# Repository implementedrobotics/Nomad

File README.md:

# NOMAD
NOMAD is a 12-DOF quadruped walking robot using Linear and Nonlinear Optimization Control techniques.

  - Linear and Nonlinear Model Predictive Control
  - Simultaneous Localization and Mapping
  - Remote Control Teleoperation

# Software Installation

First thing to do is setup your software/development environment to build the source code:
[Software Setup](https://github.com/implementedrobotics/Nomad/tree/master/Software).

# Hardware Installation

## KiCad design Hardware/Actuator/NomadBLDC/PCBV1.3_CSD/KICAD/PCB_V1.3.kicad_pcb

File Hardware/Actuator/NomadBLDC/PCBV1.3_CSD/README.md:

# File structure
* Directory - KICAD
** Contains all files for the kicad project
* Directory - KICAD_READERS
** python macros that generated BOM lists for PCBA
* Directory - GERBERS
** plots for PCBA

# Updates from original BK board
* converted from eagle to kicad
* re-routed nearly all traces
* added [CSD88599Q5DC](http://www.ti.com/lit/ds/symlink/csd88599q5dc.pdf?HQS=TI-null-null-mousermode-df-pf-null-wwe&DCM=yes&ref_url=https%3A%2F%2Fwww.mouser.com%2F&distId=26) half-bridge FET
* added more caps
* added power terminal tabs for easier soldering
* added jumper to enable/disable 120 ohm CAN terminating resistor
* added USB connector
* added I/O pin to programming connector
* simplified mask to read all components

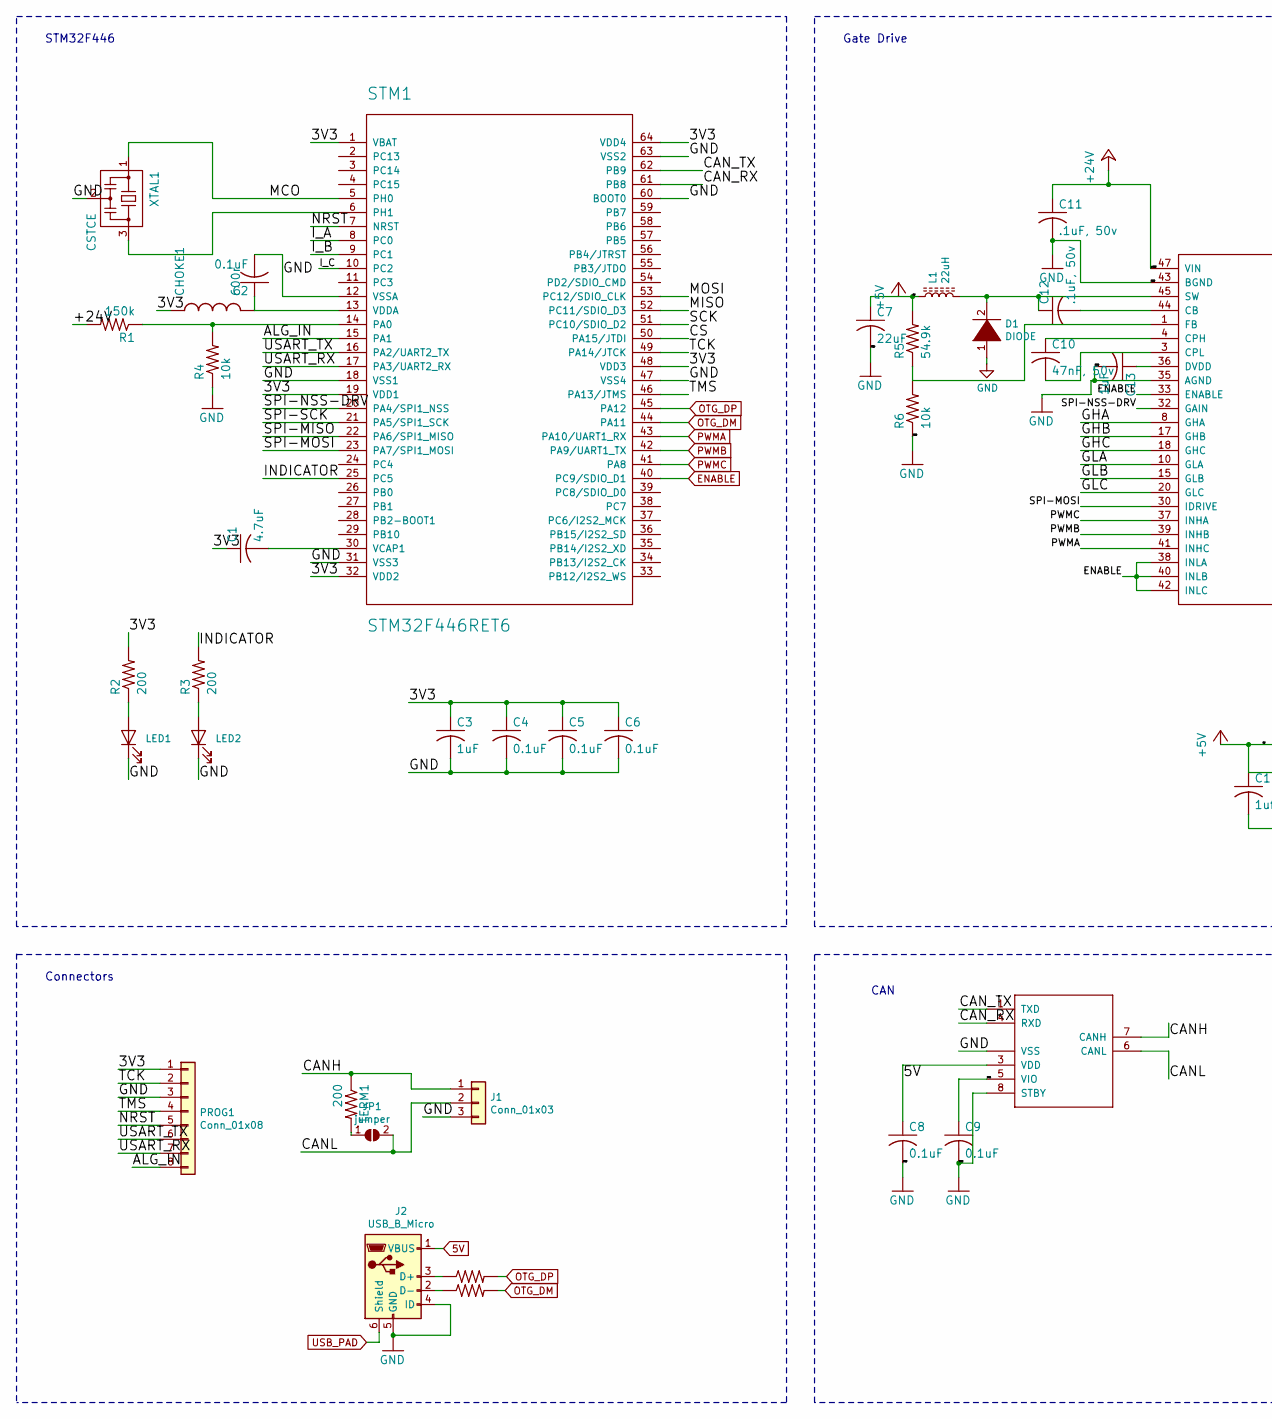
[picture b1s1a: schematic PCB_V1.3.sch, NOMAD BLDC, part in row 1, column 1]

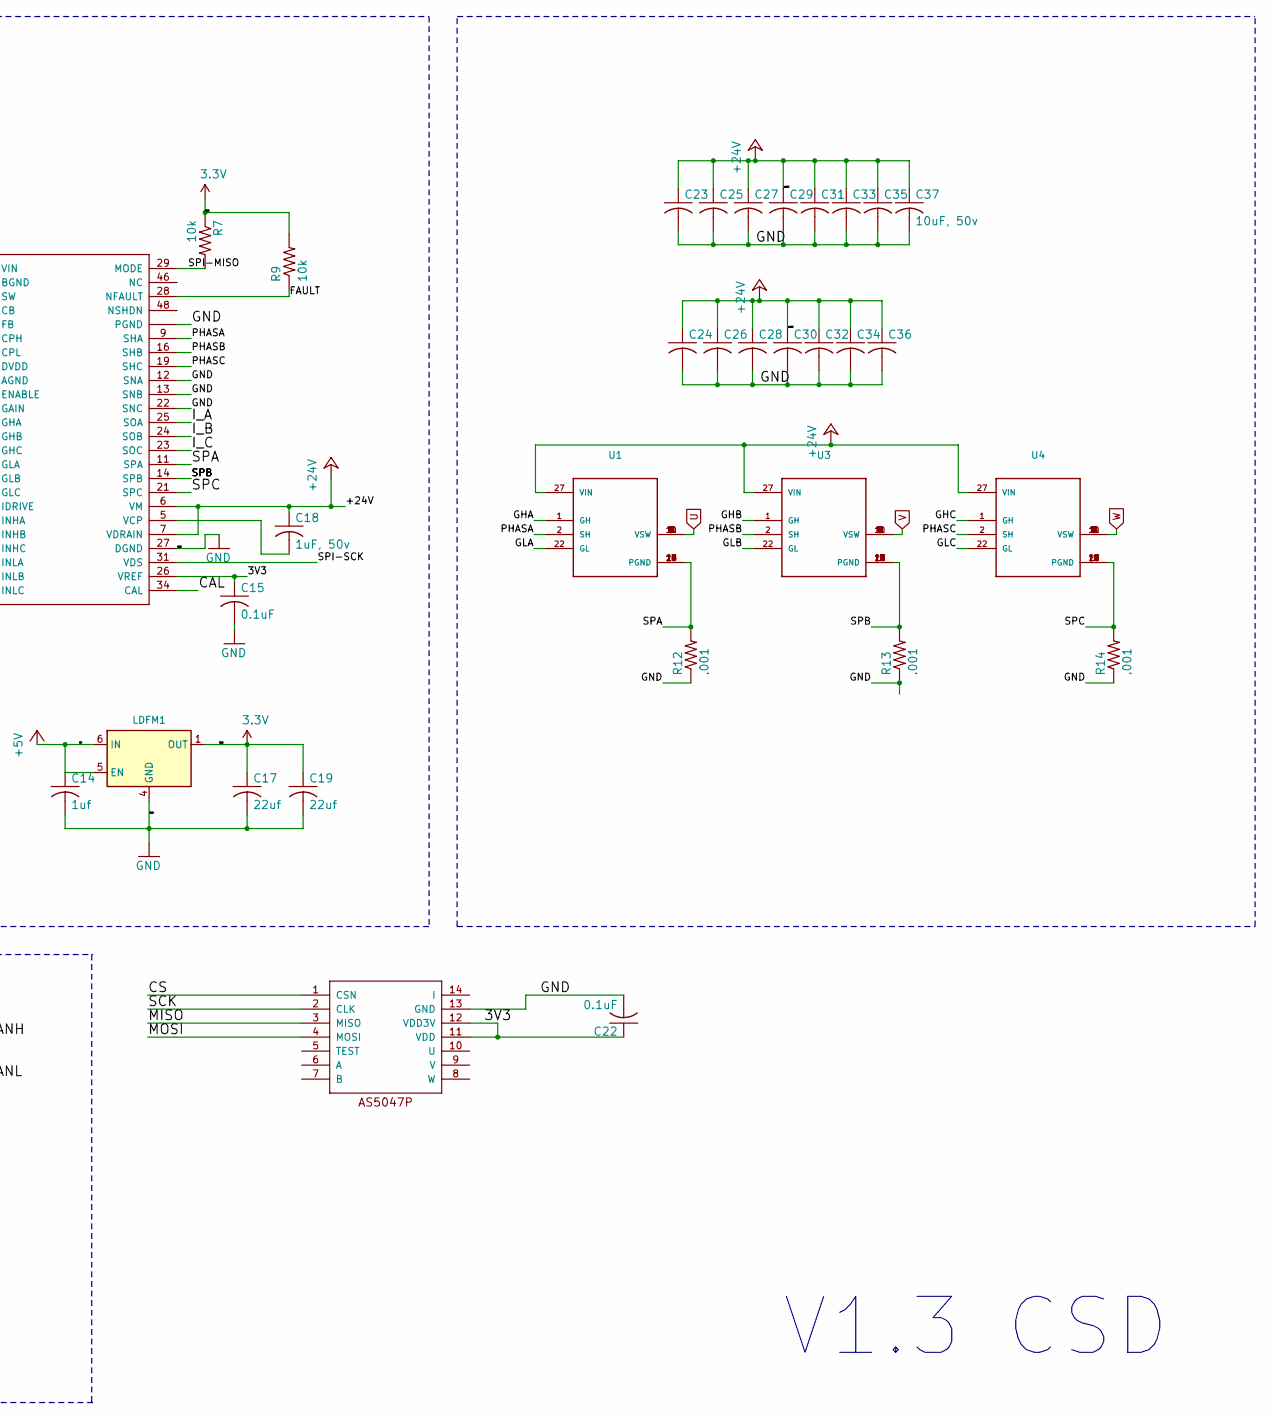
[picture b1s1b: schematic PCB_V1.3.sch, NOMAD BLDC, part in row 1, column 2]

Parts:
AS5047P1: AS5047P; TSSOP14; MPN AS5147P-HTSM
C1: 4.7uF; C_0402_1005Metric; MPN GRM155R60J475ME87D
C2, C4, C5, C6, C8, C9, C15, C22: 0.1uF; C_0402_1005Metric; MPN C0402C104K8PAC7411
C3, C13: 1uF; C_0402_1005Metric; MPN C0402C105K8PACTU
C7: 22uF; C_0603_1608Metric; MPN GRM188R61A226ME15J
C10: 47nF, 50v; C_0402_1005Metric; MPN CC0402JRX7R9BB473
C11, C12: .1uF, 50v; C_0603_1608Metric; MPN CC0603JRX7R9BB104
C14: 1uf; C_0402_1005Metric; MPN C0402C105K8PACTU
C17, C19: 22uf; C_0603_1608Metric; MPN GRM188R61A226ME15J
C18: 1uF, 50v; C_0603_1608Metric; MPN CGA3E3X5R1H105K080AB
C23, C24, C25, C26, C27, C28, C29, C30, C31, C32, C33, C34, C35, C36, C37: 10uF, 50v; C_1206_3216Metric; MPN GRT31CR61H106ME01L
CAN1: MCP2542; TDFN-8-1EP_3x2mm_P0.5mm_EP1.80x1.65mm; MPN MCP2542FDT-H/MNY
CHOKE1: 600r; L_0603_1608Metric; MPN PE-0603FB601ST
D1: DIODE; D_SOD-123; MPN MBR0580S1-7
DRV1: DRV8323RH; Texas_S-PVQFN-N48_EP5.15x5.15mm_Islands; MPN DRV8323RSRGZT
J1: Conn_01x03; JST_SH_BM03B-SRSS-TB_1x03-1MP_P1.00mm_Vertical; MPN BM03B-SURS-TF(LF)(SN)
J2: USB_B_Micro; USB_Micro-B_GCT_USB3076-30-A; MPN USB3076-30-A
JP1: jumper; SolderJumper-2_P1.3mm_Open_RoundedPad1.0x1.5mm
L1: 22uH; SDR0302; MPN NRH3012T220MNV
LDFM1: LDFM; DFN-6-1EP_3x3mm_P1mm_EP1.5x2.4mm; MPN LDFM33PUR
LED1, LED2: LED; LED_0603_1608Metric; MPN LTST-C191KRKT
PROG1: Conn_01x08; JST_SH_SM08B-SRSS-TB_1x08-1MP_P1.00mm_Horizontal; MPN SM08B-SRSS-TB(LF)(SN)
R1: 150k; R_0402_1005Metric; MPN RC0402DR-07150KL
R2, R3: 200; R_0402_1005Metric; MPN RC0402JR-07200RL
R4, R6, R7, R9: 10k; R_0402_1005Metric; MPN RT0402DRE0710KL
R5: 54.9k; R_0402_1005Metric; MPN RC0402FR-0754K9L
R8, R10: 22; R_0402_1005Metric; MPN RC0402JR-0722RL
R12, R13, R14: .001; R_1210_3225Metric; MPN PMR25HZPFV1L00
STM1: STM32F446RET6; TQFP-64_10x10mm_P0.5mm; MPN STM32F446RET6
TERM1: 200; R_0402_1005Metric; MPN RC0402JR-07200RL
U1, U3, U4: CSD88599Q5DC; MOSFET_CSD88599Q5DC; MPN CSD88599Q5DC
XTAL1: CSTCE; MPN CSTNE8M00GH5L000R0

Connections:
3.3V: AS5047P1.11 (VDD), AS5047P1.12 (VDD3V), C1.1, C3.1, C4.1, C5.1, C6.1, C9.1, C15.1, C17.1, C19.1, C22.1, CAN1.5 (VIO), CHOKE1.1, DRV1.26 (VREF), LDFM1.1 (OUT), PROG1.1, R2.2, R7.1, R9.2, STM1.1 (VBAT), STM1.19 (VDD1), STM1.32 (VDD2), STM1.48 (VDD3), STM1.64 (VDD4)
5V: C7.1, C8.1, C14.1, CAN1.3 (VDD), J2.1 (VBUS), L1.1, LDFM1.5 (EN), LDFM1.6 (IN), R5.2
+24V: C11.1, C18.1, C23.1, C24.1, C25.1, C26.1, C27.1, C28.1, C29.1, C30.1, C31.1, C32.1, C33.1, C34.1, C35.1, C36.1, C37.1, DRV1.6 (VM), DRV1.7 (VDRAIN), DRV1.47 (VIN), R1.2, U1.27 (VIN), U3.27 (VIN), U4.27 (VIN)
/ALG_IN: PROG1.8, STM1.15 (PA1)
/CAL: DRV1.34 (CAL)
/CANH: CAN1.7 (CANH), J1.1, TERM1.1
/CANL: CAN1.6 (CANL), J1.2, JP1.2 (B)
/CAN_RX: CAN1.4 (RXD), STM1.61 (PB8)
/CAN_TX: CAN1.1 (TXD), STM1.62 (PB9)
/CS: AS5047P1.1 (CSN), STM1.50 (PA15/JTDI)
/FAULT: DRV1.28 (NFAULT), R9.1
/GHA: DRV1.8 (GHA), U1.1 (GH)
/GHB: DRV1.17 (GHB), U3.1 (GH)
/GHC: DRV1.18 (GHC), U4.1 (GH)
/GLA: DRV1.10 (GLA), U1.22 (GL)
/GLB: DRV1.15 (GLB), U3.22 (GL)
/GLC: DRV1.20 (GLC), U4.22 (GL)
/INDICATOR: R3.2, STM1.25 (PC5)
/I_A: DRV1.25 (SOA), STM1.8 (PC0)
/I_B: DRV1.24 (SOB), STM1.9 (PC1)
/I_C: DRV1.23 (SOC), STM1.10 (PC2)
/MCO: STM1.5 (PH0), XTAL1.1
/MISO: AS5047P1.3 (MISO), STM1.52 (PC11/SDIO_D3)
/MOSI: AS5047P1.4 (MOSI), STM1.53 (PC12/SDIO_CLK)
/NRST: PROG1.5, STM1.7 (NRST)
/PHASA: DRV1.9 (SHA), U1.2 (SH)
/PHASB: DRV1.16 (SHB), U3.2 (SH)
/PHASC: DRV1.19 (SHC), U4.2 (SH)
/SCK: AS5047P1.2 (CLK), STM1.51 (PC10/SDIO_D2)
/SPA: DRV1.11 (SPA), R12.2, U1.12 (PGND), U1.13 (PGND), U1.14 (PGND), U1.15 (PGND), U1.16 (PGND), U1.17 (PGND), U1.18 (PGND), U1.19 (PGND), U1.20 (PGND)
/SPB: DRV1.14 (SPB), R13.2, U3.12 (PGND), U3.13 (PGND), U3.14 (PGND), U3.15 (PGND), U3.16 (PGND), U3.17 (PGND), U3.18 (PGND), U3.19 (PGND), U3.20 (PGND)
/SPC: DRV1.21 (SPC), R14.2, U4.12 (PGND), U4.13 (PGND), U4.14 (PGND), U4.15 (PGND), U4.16 (PGND), U4.17 (PGND), U4.18 (PGND), U4.19 (PGND), U4.20 (PGND)
/SPI-MISO: DRV1.29 (MODE), R7.2, STM1.22 (PA6/SPI1_MISO)
/SPI-MOSI: DRV1.30 (IDRIVE), STM1.23 (PA7/SPI1_MOSI)
/SPI-NSS-DRV: DRV1.32 (GAIN), STM1.20 (PA4/SPI1_NSS)
/SPI-SCK: DRV1.31 (VDS), STM1.21 (PA5/SPI1_SCK)
/TCK: PROG1.2, STM1.49 (PA14/JTCK)
/TMS: PROG1.4, STM1.46 (PA13/JTMS)
/USART_RX: PROG1.7, STM1.17 (PA3/UART2_RX)
/USART_TX: PROG1.6, STM1.16 (PA2/UART2_TX)
ENABLE: DRV1.33 (ENABLE), DRV1.38 (INLA), DRV1.40 (INLB), DRV1.42 (INLC), STM1.40 (PC9/SDIO_D1)
GND: AS5047P1.13 (GND), C2.2, C3.2, C4.2, C5.2, C6.2, C7.2, C8.2, C9.2, C11.2, C13.2, C14.2, C15.2, C17.2, C19.2, C22.2, C23.2, C24.2, C25.2, C26.2, C27.2, C28.2, C29.2, C30.2, C31.2, C32.2, C33.2, C34.2, C35.2, C36.2, C37.2, CAN1.2 (VSS), CAN1.8 (STBY), CAN1.9 (VSS), D1.1 (K), DRV1.2 (PGND), DRV1.12 (SNA), DRV1.13 (SNB), DRV1.22 (SNC), DRV1.27 (DGND), DRV1.35 (AGND), DRV1.43 (BGND), DRV1.49 (PGND), J1.3, J2.4 (ID), J2.5 (GND), LDFM1.4 (GND), LED1.1 (K), LED2.1 (K), PROG1.3, R4.1, R6.1, R12.1, R13.1, R14.1, STM1.12 (VSSA), STM1.18 (VSS1), STM1.31 (VSS3), STM1.47 (VSS4), STM1.60 (BOOT0), STM1.63 (VSS2), XTAL1.2
unnamed: C1.2, STM1.30 (VCAP1)
unnamed: C2.1, CHOKE1.2, STM1.13 (VDDA)
unnamed: C10.1, DRV1.4 (CPH)
unnamed: C10.2, DRV1.3 (CPL)
unnamed: C12.1, D1.2 (A), DRV1.45 (SW), L1.2
unnamed: C12.2, DRV1.44 (CB)
unnamed: C13.1, DRV1.36 (DVDD)
unnamed: C18.2, DRV1.5 (VCP)
unnamed: DRV1.1 (FB), R5.1, R6.2
unnamed: J2.2 (D-), R8.1
unnamed: J2.3 (D+), R10.1
unnamed: JP1.1 (A), TERM1.2
unnamed: LED1.2 (A), R2.1
unnamed: LED2.2 (A), R3.1
unnamed: R1.1, R4.2, STM1.14 (PA0)
unnamed: STM1.6 (PH1), XTAL1.3
OTG_DM: R8.2, STM1.44 (PA11)
OTG_DP: R10.2, STM1.45 (PA12)
PWMA: DRV1.41 (INHC), STM1.43 (PA10/UART1_RX)
PWMB: DRV1.39 (INHB), STM1.42 (PA9/UART1_TX)
PWMC: DRV1.37 (INHA), STM1.41 (PA8)
U: U1.3 (VSW), U1.4 (VSW), U1.5 (VSW), U1.6 (VSW), U1.7 (VSW), U1.8 (VSW), U1.9 (VSW), U1.10 (VSW), U1.11 (VSW)
USB_PAD: J2.6 (Shield)
V: U3.3 (VSW), U3.4 (VSW), U3.5 (VSW), U3.6 (VSW), U3.7 (VSW), U3.8 (VSW), U3.9 (VSW), U3.10 (VSW), U3.11 (VSW)
W: U4.3 (VSW), U4.4 (VSW), U4.5 (VSW), U4.6 (VSW), U4.7 (VSW), U4.8 (VSW), U4.9 (VSW), U4.10 (VSW), U4.11 (VSW)

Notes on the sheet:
Gate Drive
STM32F446
CAN
Connectors
V1.3 CSD

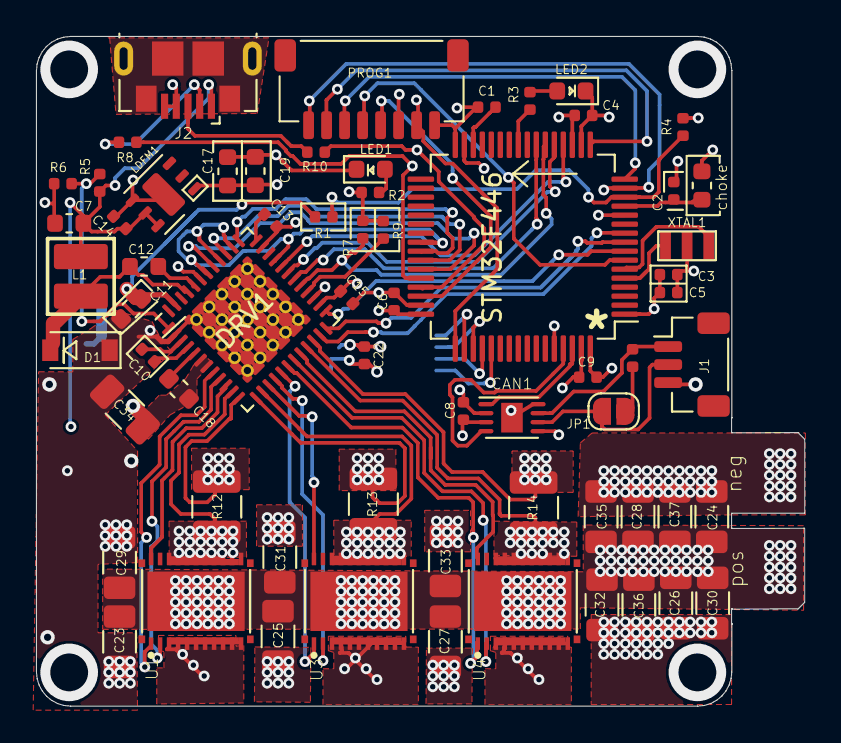
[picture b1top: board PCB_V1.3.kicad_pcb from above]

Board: 4 copper layers, 42.7 x 37.2 mm, 66 parts (0 on the bottom side), 65 nets.

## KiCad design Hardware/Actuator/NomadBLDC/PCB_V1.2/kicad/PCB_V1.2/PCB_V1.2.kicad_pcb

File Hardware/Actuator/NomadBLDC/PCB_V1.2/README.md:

## NOMAD BLDC Printed Circuit Board V1.2

Features / modifications:
  - STM32F446 microcontroller
  - Texas Instruments DRV8323 Gate Driver
  - Integrated AMS AS5147 absolute encoder
  - Daisy chained CAN connectors
  - Additional labeling to ease assembly
  - Replaced through-holes with solder pad connectors

Directory structure:
  - BOMs - spreadsheets and other forms
  - PDFS - schematic and part placement
  - kicad
    - PCB_V1.2 - files for schematic, PCB
    - gerbers  - files to order PCB from PCBWay

Board dimensions: 40mm x 38mm (w x h)

Schematic and PCB is originally based on the great work from Ben Katz. Check out his [Build Its Blog](http://build-its.blogspot.com) and open source hardware [page](https://github.com/bgkatz/3phase_integrated/).

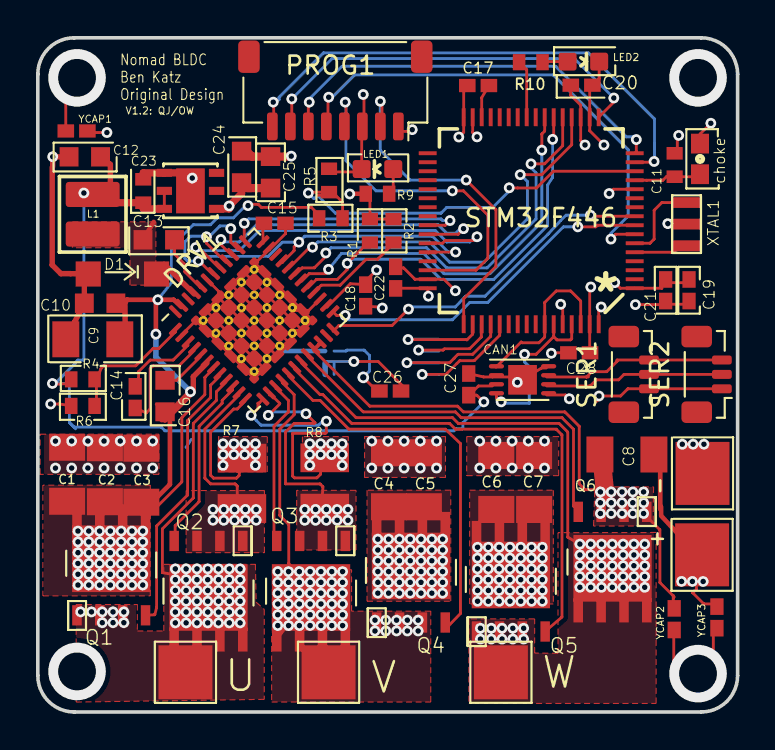
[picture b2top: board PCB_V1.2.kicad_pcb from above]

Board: 4 copper layers, 38.9 x 37.5 mm, 66 parts (0 on the bottom side), 56 nets.

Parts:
AS5047P1: AS5047P; TSSOP14
C1, C2, C3, C4, C5, C6, C7, C8, C9: 10uF, 50v; C1206K
C10, C13: 0.1uF, 50v; C0603K
C11: 100nF; C0402
C12: 22uF; C0603K
C14: 47nF, 50v; C0402K
C15, C19: 1uF; C0402K
C16: 1uF, 50v; C0603K
C17: 4.7uF; C0402K
C18, C20, C21, C22: 100nF; C0402K
C23: 1uf; C0402
C24, C25: 22uf; C0603K
C26, C27, C28: .1uF; C0402K
CAN1: MCP2542; TDFN-8-1EP_3x2mm_P0.5mm_EP1.80x1.65mm
CHOKE1: 600r; 0603
D1: DIODE-SOD123; SOD123
DRV1: DRV8323RH; Texas_S-PVQFN-N48_EP5.15x5.15mm_Islands
L1: 22uH; SDR0302
LDFM1: LDFM; DFN6-3X3
LED1, LED2: G; LED-0603
PROG1: Conn_01x08; JST_SH_SM08B-SRSS-TB_1x08-1MP_P1.00mm_Horizontal
Q1, Q2, Q3, Q4, Q5, Q6: TPH; TRANS_TPH5900CNH,L1Q
R1, R2, R5, R6: 10k; R0402
R3: 150k; R0402
R4: 54.9k; R0402
R7, R8: .001; R1210
R9, R10: 200; R0402
SER1, SER2: ?M03B-SRSS-TBS; JST_SUR_BM03B-SURS-TF_1x03-1MP_P0.80mm_Vertical
STM1: STM32F446RET6; TQFP64
U$1, U$2: 18_AWG_PAD; TestPoint_Pad_3.0x3.5mm
U$3: test_point; TestPoint_Pad_3.0x3.0mm
U$4, U$5: 18_AWG_PAD; TestPoint_Pad_3.0x3.0mm
XTAL1: CSTCE
YCAP1, YCAP2, YCAP3: 100nF; C0402K

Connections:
3.3V: AS5047P1.11, AS5047P1.12, C17.1, C18.1, C19.1, C20.1, C21.1, C22.1, C24.1, C25.1, C26.1, C28.1, CAN1.5, CHOKE1.1, DRV1.26, LDFM1.1, PROG1.1, R1.1, R2.2, R9.2, STM1.1, STM1.19, STM1.32, STM1.48, STM1.64
+5V: C12.1, C23.1, C27.1, CAN1.3, L1.1, LDFM1.5, LDFM1.6, R4.2
+24V: C1.1, C2.1, C3.1, C4.1, C5.1, C6.1, C7.1, C8.1, C9.1, C10.1, C16.1, DRV1.6, DRV1.7, DRV1.47, Q1.5, Q1.6, Q1.7, Q1.8, Q1.EP, Q4.5, Q4.6, Q4.7, Q4.8, Q4.EP, Q5.5, Q5.6, Q5.7, Q5.8, Q5.EP, R3.2, U$1.1, YCAP3.1
/ALG_IN: PROG1.8, STM1.15
/CANH: CAN1.7, SER1.3, SER2.3
/CANL: CAN1.6, SER1.2, SER2.2
/CAN_RX: CAN1.4, STM1.59, STM1.61
/CAN_TX: CAN1.1, STM1.58, STM1.62
/CS: AS5047P1.1, STM1.50
/ENABLE: DRV1.33, DRV1.38, DRV1.40, DRV1.42, STM1.44
/FAULT: DRV1.28, R2.1
/GHA: DRV1.8, Q1.4
/GHB: DRV1.17, Q4.4
/GHC: DRV1.18, Q5.4
/GLA: DRV1.10, Q2.4
/GLB: DRV1.15, Q3.4
/GLC: DRV1.20, Q6.4
/INDICATOR: R10.2, STM1.25
/I_A: DRV1.25, STM1.8
/I_B: DRV1.24, STM1.9
/MCO: STM1.5, XTAL1.1
/MISO: AS5047P1.3, STM1.52
/MOSI: AS5047P1.4, STM1.53
/N$6: YCAP2.2, YCAP3.2
/NRST: PROG1.5, STM1.7
/PHASA: DRV1.9, Q1.1, Q1.2, Q1.3, Q2.5, Q2.6, Q2.7, Q2.8, Q2.EP, U$3.1
/PHASB: DRV1.16, Q3.5, Q3.6, Q3.7, Q3.8, Q3.EP, Q4.1, Q4.2, Q4.3, U$4.1
/PHASC: DRV1.19, Q5.1, Q5.2, Q5.3, Q6.5, Q6.6, Q6.7, Q6.8, Q6.EP, U$5.1
/PWMA: DRV1.41, STM1.43
/PWMB: DRV1.39, STM1.42
/PWMC: DRV1.37, STM1.41
/SCK: AS5047P1.2, STM1.51
/SPA: DRV1.11, Q2.1, Q2.2, Q2.3, R7.2
/SPB: DRV1.14, Q3.1, Q3.2, Q3.3, R8.2
/SPI-MISO: DRV1.29, R1.2, STM1.22
/SPI-MOSI: DRV1.30, STM1.23
/SPI-NSS-DRV: DRV1.32, STM1.20
/SPI-SCK: DRV1.31, STM1.21
/TCK: PROG1.2, STM1.49
/TMS: PROG1.4, STM1.46
/USART_RX: PROG1.7, STM1.17
/USART_TX: PROG1.6, STM1.16
GND: AS5047P1.13, C1.2, C2.2, C3.2, C4.2, C5.2, C6.2, C7.2, C8.2, C9.2, C10.2, C11.2, C12.2, C15.2, C18.2, C19.2, C20.2, C21.2, C22.2, C23.2, C24.2, C25.2, C26.2, C27.2, C28.2, CAN1.2, CAN1.8, CAN1.9, D1.A, DRV1.2, DRV1.12, DRV1.13, DRV1.21, DRV1.22, DRV1.27, DRV1.35, DRV1.43, DRV1.49, LDFM1.4, LDFM1.EXP, LED1.C, LED2.C, PROG1.3, Q6.1, Q6.2, Q6.3, R5.1, R6.1, R7.1, R8.1, SER1.1, SER2.1, STM1.12, STM1.18, STM1.31, STM1.47, STM1.60, STM1.63, U$2.1, XTAL1.2, YCAP1.1, YCAP2.1
unnamed: C11.1, CHOKE1.2, STM1.13
unnamed: C13.1, D1.C, DRV1.45, L1.2
unnamed: C13.2, DRV1.44
unnamed: C14.1, DRV1.4
unnamed: C14.2, DRV1.3
unnamed: C15.1, DRV1.36
unnamed: C16.2, DRV1.5
unnamed: C17.2, STM1.30
unnamed: DRV1.1, R4.1, R6.2
unnamed: LED1.A, R9.1
unnamed: LED2.A, R10.1
unnamed: R3.1, R5.2, STM1.14
unnamed: STM1.6, XTAL1.3

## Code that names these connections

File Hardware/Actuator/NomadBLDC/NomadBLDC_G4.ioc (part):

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Mcu.Name=STM32G474R(B-C-E)Tx
Mcu.Package=LQFP64
Mcu.UserName=STM32G474RETx
PA0.GPIOParameters=GPIO_Label
PA0.GPIO_Label=VBUS_IN
PA0.Mode=IN1-Single-Ended
PA0.Signal=ADC1_IN1
PA10.GPIOParameters=GPIO_Label
PA10.GPIO_Label=PWM_A
PA10.Signal=S_TIM1_CH3
PA11.Mode=Device
PA11.Signal=USB_DM
PA12.Mode=Device
PA12.Signal=USB_DP
PA13.Signal=SYS_JTMS-SWDIO
PA14.Signal=SYS_JTCK-SWCLK
PA15.GPIOParameters=GPIO_Label
PA15.GPIO_Label=ENCODER_SPI_CS
PA15.Mode=NSS_Signal_Hard_Output
PA15.Signal=SPI3_NSS
PA2.Mode=Asynchronous
PA2.Signal=USART2_TX
PA3.Mode=Asynchronous
PA3.Signal=USART2_RX
PA4.Mode=NSS_Signal_Hard_Output
PA4.Signal=SPI1_NSS
PA5.Mode=Full_Duplex_Master
PA5.Signal=SPI1_SCK
PA6.Mode=Full_Duplex_Master
PA6.Signal=SPI1_MISO
PA7.Mode=Full_Duplex_Master
PA7.Signal=SPI1_MOSI
PA8.GPIOParameters=GPIO_Label
PA8.GPIO_Label=PWM_C
PA8.Signal=S_TIM1_CH1
PA9.GPIOParameters=GPIO_Label
PA9.GPIO_Label=PWM_B
PA9.Signal=S_TIM1_CH2
PB3.GPIOParameters=GPIO_Label
PB3.GPIO_Label=CAN_RX
PB3.Mode=FDCANSlave
PB3.Signal=FDCAN3_RX
PB4.GPIOParameters=GPIO_Label
PB4.GPIO_Label=CAN_TX
PB4.Mode=FDCANSlave
PB4.Signal=FDCAN3_TX
PC0.GPIOParameters=GPIO_Label
PC0.GPIO_Label=I_A
PC0.Mode=IN6-Single-Ended
PC0.Signal=ADC1_IN6
PC1.GPIOParameters=GPIO_Label
PC1.GPIO_Label=I_B
PC1.Mode=IN7-Single-Ended
PC1.Signal=ADC1_IN7
PC10.GPIOParameters=GPIO_Label
PC10.GPIO_Label=ENCODER_SPI_CLK
PC10.Mode=Full_Duplex_Master
PC10.Signal=SPI3_SCK
PC11.GPIOParameters=GPIO_Label
PC11.GPIO_Label=ENCODER_SPI_MISO
PC11.Mode=Full_Duplex_Master
PC11.Signal=SPI3_MISO
PC12.GPIOParameters=GPIO_Label
PC12.GPIO_Label=ENCODER_SPI_MOSI
PC12.Mode=Full_Duplex_Master
PC12.Signal=SPI3_MOSI
PC2.GPIOParameters=GPIO_Label
PC2.GPIO_Label=I_C
PC2.Mode=IN8-Single-Ended
PC2.Signal=ADC1_IN8
PC4.GPIOParameters=GPIO_Label
PC4.GPIO_Label=CONN_GPIO
PC4.Signal=GPIO_Output
PC5.GPIOParameters=GPIO_Label
PC5.GPIO_Label=LED
PC5.Signal=GPIO_Output
PC9.GPIOParameters=GPIO_Label
PC9.GPIO_Label=DRV_ENABLE
PC9.Signal=GPIO_Output
PF0-OSC_IN.Mode=HSE-External-Oscillator
PF0-OSC_IN.Signal=RCC_OSC_IN
PF1-OSC_OUT.Mode=HSE-External-Oscillator
PF1-OSC_OUT.Signal=RCC_OSC_OUT
RCC.HSE_VALUE=8000000
RCC.SYSCLKFreq_VALUE=170000000
RCC.SYSCLKSource=RCC_SYSCLKSOURCE_PLLCLK
board=custom

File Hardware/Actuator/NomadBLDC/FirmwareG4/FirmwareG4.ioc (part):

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Mcu.Name=STM32G474C(B-C-E)Ux
Mcu.Package=UFQFPN48
Mcu.UserName=STM32G474CEUx
PA0.GPIOParameters=GPIO_Speed,GPIO_Label
PA0.GPIO_Label=ENC_A
PA0.GPIO_Speed=GPIO_SPEED_FREQ_LOW
PA0.Signal=S_TIM2_CH1
PA1.GPIOParameters=GPIO_Speed,GPIO_Label
PA1.GPIO_Label=ENC_B
PA1.GPIO_Speed=GPIO_SPEED_FREQ_LOW
PA1.Signal=S_TIM2_CH2
PA10.GPIOParameters=GPIO_Speed,GPIO_Label
PA10.GPIO_Label=DRV_MISO
PA10.GPIO_Speed=GPIO_SPEED_FREQ_HIGH
PA10.Mode=Full_Duplex_Master
PA10.Signal=SPI2_MISO
PA13.GPIOParameters=GPIO_Label
PA13.GPIO_Label=TMS
PA13.Mode=Serial_Wire
PA13.Signal=SYS_JTMS-SWDIO
PA14.GPIOParameters=GPIO_Label
PA14.GPIO_Label=TCK
PA14.Mode=Serial_Wire
PA14.Signal=SYS_JTCK-SWCLK
PA15.GPIOParameters=GPIO_PuPd,GPIO_Label
PA15.GPIO_Label=DRV_nFAULT
PA15.GPIO_PuPd=GPIO_PULLUP
PA15.Signal=GPIO_Input
PA2.GPIOParameters=GPIO_Speed,GPIO_Label
PA2.GPIO_Label=USART_TX
PA2.GPIO_Speed=GPIO_SPEED_FREQ_VERY_HIGH
PA2.Mode=Asynchronous
PA2.Signal=USART2_TX
PA3.GPIOParameters=GPIO_Speed,GPIO_Label
PA3.GPIO_Label=USART_RX
PA3.GPIO_Speed=GPIO_SPEED_FREQ_VERY_HIGH
PA3.Mode=Asynchronous
PA3.Signal=USART2_RX
PA4.GPIOParameters=GPIO_Label
PA4.GPIO_Label=ENC_CS
PA4.Signal=GPIO_Output
PA5.GPIOParameters=GPIO_Speed,GPIO_Label
PA5.GPIO_Label=ENC_SCK
PA5.GPIO_Speed=GPIO_SPEED_FREQ_VERY_HIGH
PA5.Mode=Full_Duplex_Master
PA5.Signal=SPI1_SCK
PA6.GPIOParameters=GPIO_Speed,GPIO_Label
PA6.GPIO_Label=ENC_MISO
PA6.GPIO_Speed=GPIO_SPEED_FREQ_VERY_HIGH
PA6.Mode=Full_Duplex_Master
PA6.Signal=SPI1_MISO
PA7.GPIOParameters=GPIO_Speed,GPIO_Label
PA7.GPIO_Label=ENC_MOSI
PA7.GPIO_Speed=GPIO_SPEED_FREQ_VERY_HIGH
PA7.Mode=Full_Duplex_Master
PA7.Signal=SPI1_MOSI
PA8.GPIOParameters=GPIO_Label
PA8.GPIO_Label=EXT_TEMP
PA8.Mode=IN1-Single-Ended
PA8.Signal=ADC5_IN1
PA9.GPIOParameters=GPIO_Label
PA9.GPIO_Label=BATT_IN
PA9.Mode=IN2-Single-Ended
PA9.Signal=ADC5_IN2
PB0.GPIOParameters=GPIO_Label
PB0.GPIO_Label=I_B
PB0.Mode=IN12-Single-Ended
PB0.Signal=ADC3_IN12
PB1.GPIOParameters=GPIO_Label
PB1.GPIO_Label=I_C
PB1.Mode=IN12-Single-Ended
PB1.Signal=ADC1_IN12
PB10.GPIOParameters=GPIO_Label
PB10.GPIO_Label=LED_STATUS
PB10.Signal=GPIO_Output
PB12.GPIOParameters=GPIO_Label
PB12.GPIO_Label=DRV_CS
PB12.Signal=GPIO_Output
PB13.GPIOParameters=GPIO_Speed,GPIO_Label
PB13.GPIO_Label=DRV_SCK
PB13.GPIO_Speed=GPIO_SPEED_FREQ_HIGH
PB13.Mode=Full_Duplex_Master
PB13.Signal=SPI2_SCK
PB14.GPIOParameters=GPIO_Label
PB14.GPIO_Label=FET_TEMP
PB14.Mode=IN4-Single-Ended
PB14.Signal=ADC4_IN4
PB15.GPIOParameters=GPIO_Speed,GPIO_Label
PB15.GPIO_Label=DRV_MOSI
PB15.GPIO_Speed=GPIO_SPEED_FREQ_HIGH
PB15.Mode=Full_Duplex_Master
PB15.Signal=SPI2_MOSI
PB3.GPIOParameters=GPIO_Speed,GPIO_Label
PB3.GPIO_Label=CAN_RX
PB3.GPIO_Speed=GPIO_SPEED_FREQ_HIGH
PB3.Mode=FDCANFD
PB3.Signal=FDCAN3_RX
PB4.GPIOParameters=GPIO_Speed,GPIO_Label
PB4.GPIO_Label=CAN_TX
PB4.GPIO_Speed=GPIO_SPEED_FREQ_HIGH
PB4.Mode=FDCANFD
PB4.Signal=FDCAN3_TX
PB5.GPIOParameters=GPIO_Label
PB5.GPIO_Label=DRV_ENABLE
PB5.Signal=GPIO_Output
PB6.GPIOParameters=GPIO_Speed,GPIO_Label
PB6.GPIO_Label=PWM_A
PB6.GPIO_Speed=GPIO_SPEED_FREQ_LOW
PB6.Signal=S_TIM8_CH1
PB8-BOOT0.GPIOParameters=GPIO_Speed,GPIO_Label
PB8-BOOT0.GPIO_Label=PWM_B
PB8-BOOT0.GPIO_Speed=GPIO_SPEED_FREQ_LOW
PB8-BOOT0.Signal=S_TIM8_CH2
PB9.GPIOParameters=GPIO_Speed,GPIO_Label
PB9.GPIO_Label=PWM_C
PB9.GPIO_Speed=GPIO_SPEED_FREQ_LOW
PB9.Signal=S_TIM8_CH3
PC4.GPIOParameters=GPIO_Label
PC4.GPIO_Label=I_A
PC4.Mode=IN5-Single-Ended
PC4.Signal=ADC2_IN5
PC6.GPIOParameters=GPIO_Label
PC6.GPIO_Label=USER_GPIO
PC6.Signal=GPIO_Output
PF0-OSC_IN.Mode=HSE-External-Oscillator
PF0-OSC_IN.Signal=RCC_OSC_IN
PF1-OSC_OUT.Mode=HSE-External-Oscillator
PF1-OSC_OUT.Signal=RCC_OSC_OUT
RCC.HSE_VALUE=8000000
RCC.SYSCLKFreq_VALUE=170000000
RCC.SYSCLKSource=RCC_SYSCLKSOURCE_PLLCLK
board=custom

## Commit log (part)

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2020-07-02 Fix vtable issue. Starting to add control states
2020-07-02 Control State Machine Started. Ready to compute force outputs
2020-07-02 Add nomad dynamics handler task
2020-07-03 Quick Push
2020-07-03 Working on Kinematics/Dynamics Task
2020-07-07 Jacobian in dynamics finished up.
2020-07-16 Add simulation interface
2020-07-17 Work on gazebo loading
2020-07-20 Working on sim.
2020-07-20 Fix sim compile issue. Starting ZCM
2020-07-21 Dart Sim Publishing State
2020-07-22 More collsions
2020-07-22 Simplifed URDF collision model is complete (good enough)
2020-07-22 Simulation Interface is Connected to Simulation
2020-07-28 Work on estimators.
2020-07-29 Begin Port refactoring. Switching back to less generic types
2020-07-31 Bringing in Dynamics Computation Task
2020-07-31 Refactor Port namespace from Realtime->Communications
2020-07-31 Updated RT memory allocation and checking
2020-07-31 More refactoring. Ready to flesh out FSM now for Stand up!
2020-08-01 Fix decode bug
2020-08-01 Move Operator Interface
2020-08-01 State Machine Transition Ready
2020-08-01 Cleanup FSM debug
2020-08-03 Update namespaces to C++17
2020-08-03 Fixing Time vars
2020-08-04 Update Time Routines
2020-08-04 Much better time functionss
2020-08-04 State Machine/Tme Statisicts
2020-08-05 Misc.
2020-08-05 Add Leg control message
2020-08-06 Updating Control Data Class
2020-08-07 Fixing Bugs
2020-08-07 Refactoring. FSM sending control msg now.
2020-08-09 A bit broken. Working on control instability.
2020-08-10 UDP Jitter needs fixing.
2020-08-10 Still working on control timing...
2020-08-11 Pre merge
2020-08-12 New native thread port added.
2020-08-13 Send needs to be faster?
2020-08-13 Added Native Threading. May still be some issues with RT scheduling.
2020-08-13 Working on standup
2020-08-14 Better, still some issues.
2020-08-16 Update/Broken
2020-08-16 Change out timer code for better efficiency. System Block Diagrams coming along.
2020-08-17 Add varying sample rates
2020-08-17 Start Task Nodes
2020-08-17 End of day.
2020-08-18 Convert control/fsm nodes to new block diagram model.
2020-08-18 Bug Fixes
2020-08-18 Release is broken for some reason.
2020-08-19 Conver the leg controller task. Next is teleop
2020-08-19 MUCH Better! Stand PD is stable. This seems much better than previous async impl.
2020-08-20 Fix qpoases linker bug
2020-08-22 End of Friday.
2020-08-22 Working on QP Solver Class. Almost there...
2020-08-23 Almost there! Still need to code the constraints
2020-08-23 QP almost there. Couple of bugs. Branch to fix.
2020-08-24 Fixed. Was a row/col order issue on non-symmetric constraints matrix A_qp
2020-08-24 Update CMake. Move helpers to mathutils
2020-08-24 Stand is working with the QP!
2020-08-25 Cleanups. Standup/Orientation working very well with new inertians.
2020-08-25 Body Pose from Gamepad is working.
2020-08-25 Working on Rotated Yaw Coordinates
2020-08-26 Still ahve issues with rotated yaw...
2020-08-27 Update Rotation Helpers
2020-08-27 This commit was all testing and can be undid...
2020-08-28 Problem between base link and body_node
2020-08-28 Found the culprit. SetPositions is not as it seems...
2020-08-28 A little cleanup. But still lost qp stability
2020-08-29 Slight teak to initial stand condition
2020-08-30 Update Jacobian stuff in Nomad Dynamics
2020-08-30 Add some center of support code
2020-08-30 Change back to world coordinate in dynamics block
2020-08-31 Quick Commit. Broken
2020-09-02 Start G4 Firmware for next iteration of BLDC
2020-09-02 Create Branch
2020-09-06 Add G4 Branch
2020-09-08 Got Task Linking
2020-09-09 Getting Threads in
2020-09-10 Remove build folder
2020-09-10 Need to map interrupts better
2020-09-11 Update SVD
2020-09-13 Ready to get UART Working
2020-09-14 Good MX Build
2020-09-14 UART DMA RX Working.
2020-09-16 Fix ISR Bug. USART is ready to roll now.
2020-09-16 Add HDLC and CRC to UART
2020-09-16 Refactor. Add HDLC and Logging back in.
2020-09-17 Chnage type back to HDLC
2020-09-17 Switch to main.cpp
2020-09-17 Fix CPP error
2020-09-18 Proper RTOS/C++ Bringup. Ends up being a HEAP size issue
2020-09-18 About to add DSP Libs
2020-09-18 Add DSP Functions (Plus way too many others... But this works for now.)
2020-09-19 Add Queue to Service
2020-09-21 Got Position Sensor SPI Working
2020-09-22 Add Flash Support
2020-09-22 Change Flash Address Page
2020-09-22 Start DRV SPI Driver
2020-09-22 Updating DRV8323 driver
2020-09-23 DRV8323 is communicating. Need to finish all the access functions.
2020-09-23 Tweak Masks
2020-09-23 Fix bugs. Need to reverify defaults
2020-09-24 DRV Working Correctly. Start Adding Motor Objects
2020-09-24 Add Remaining files. Still need to port.
2020-09-24 Update LED Tasks
2020-09-24 Add inturrupts into MX
2020-09-24 Fixing Timers
2020-09-24 ADC/Timers Ready for Testing
2020-09-26 Timer Testing
2020-09-26 More Timer Updates
2020-09-27 Working on ADC
2020-09-27 Trying to track down LL ADC Issue
2020-09-27 ADC Works with HAL. Will attempt LL again.
2020-09-27 HAL/LL Working. Now try to isolate LL issue
2020-09-27 LL ADC. About to tie back in to timers
2020-09-27 FINALLY LL_ADC + LL_TIM synced. CubeMX with the L again...
2020-09-28 Final Commit of Day. Fix ADC accuracy bug with vbus
2020-09-28 Fix Phase Ordering in SetDuty
2020-09-29 Fix DRV Enable/Disable. Misc. Cleaup.
2020-09-29 Some more updates.
2020-09-30 Turn and Spin
2020-10-01 Start UART refactor to CPP
2020-10-02 BROKE. Working on new UART
2020-10-04 Progress on CPP conversion of UART
2020-10-04 C++ UART Done. Need HDLC receive/callback handle.
2020-10-05 Comment
2020-10-14 HDLC and UI working Now. Refactor UART. Fix measurement updates
2020-10-15 UI Update
2020-10-15 Add CCM Support. Still needs testing.
2020-10-16 Add Thermistor Class
2020-10-16 Thermistor Compute Function
2020-10-16 Thermistor Object Working.
2020-10-17 Compile fix for previous commit
2020-10-17 Cordic Working
2020-10-17 Replace arm math functions
2020-10-17 Cordic testing
2020-10-17 Time to optimize a few functions to get loop time for 40 khz
2020-10-17 Fix UI
2020-10-18 Add LPF
2020-10-18 Update TODO
2020-10-18 Update IOC, Remove old Firmware
2020-10-18 Time to branch for FSM refactor
2020-10-18 Add FSM Classes
2020-10-19 Working through adding FSM
2020-10-20 Starting ADC Perifpheral
2020-10-20 ADC Finished. Need Testing.
2020-10-20 TODO Edits
2020-10-21 Good push for the ADC peripheral. Further refactoring of the Motor Controller and removing lots of old globals
2020-10-22 Fixed ADC Bugs/Peripheral is Functional TIL ADC Overrun implications... FSM code is working
2020-10-22 Inductance Measurement Added Back
2020-10-22 Add Phase Order Measurements
2020-10-23 Encoder Offset Calibration Added Updated FSM Functionality Cleanup ADC
2020-10-23 Add FOC Voltage. Something is broken here...
2020-10-25 Add back CCM. Reduce RTOS Heap Size.
2020-10-25 Reduce memory of state machine. Add enum types for state ids
2020-10-25 Add Phase Order Compute
2020-10-26 Add new states.
2020-10-26 Add other FOC control states. Full functionality has returned. 40khz + Comms is stable.
2020-10-27 Cleanup. Add RMS Back. Update RIng Buffer Inlining
2020-10-27 TODO Update
2020-10-27 Was current sense noise with split start/end position sensor reads. Remved for now.
2020-10-27 Add Bus Current
2020-10-28 Bus Current is added back/working.
2020-10-28 Remove math_ops.h
2020-10-28 Bug fix with null/lockup error on cold boot
2020-10-29 Update UI
2020-10-29 Upadtes
2020-10-29 Update Python Data Container
2020-10-30 Start FD CAN Testing
2020-10-30 Getting some bytes out over FD CAN
2020-10-31 Fix readme typo
2020-10-31 Test
2020-11-01 Workign through can bitrates
2020-11-02 CAN BUG FIXED!! Damn you CubeMX!!!
2020-11-02 FD Can vetted and working with PEAK CAN USB
2020-11-02 Settings for 1mbps/2mbps brs
2020-11-04 Adding FDCAN perph
2020-11-06 Update FDCAN
2020-11-06 Add FD CAN Periph
2020-11-06 FDCAN Peripheral Working. Next is receive functionality.
2020-11-07 Still have interrupt problems. Trying some refactor
2020-11-07 Interrupts working. Now adding Callbacks
2020-11-07 Callbacks implemented. Almost ready to PR.
2020-11-07 Slight cleanup.
2020-11-10 Start Working on Registers
2020-11-11 Template Added
2020-11-11 More Register Interfacing
2020-11-12 Some more register work
2020-11-13 Add more struct support.
2020-11-14 PR FDCAN
2020-11-14 Starting Register Layout
2020-11-15 Add device status Register
2020-11-15 Add More Registers. Also probably broke the GUI Serial Protocol
2020-11-15 Increase main task heap a bit
2020-11-15 Got socketcan working. Ready for PC Control->BLDC loop testing.
2020-11-18 Add Motor Controller Config Registers
2020-11-18 More reg defs..
2020-11-18 Regs...
2020-11-18 Last of registers for now.
2020-11-22 Remapped Structs for better order. DEFAULTS.
2020-11-22 Reset back to neutral defaults. Update TODO.
2020-11-26 Update python data containers for refactor
2020-11-26 Ready to merge to master
2020-12-01 Change can config
2021-01-20 Fix Allocation Bug. Still should move encoder calibration -> PC Side.
2021-03-03 Fix Phase Order instability bug. Make sure to get this in master.
2021-03-05 Add a little hisotresis to position limits
2021-03-05 Gear ratio fix for mechanical position.
2021-03-07 CAN Communications updates
2021-03-07 Working PC -> NomadBLDC over CAN. A little rough but working.
2021-03-08 Struct retrieval.
2021-03-09 Getting some more commands going. Bug Fixes
2021-03-13 Rework Flash Save.Load
2021-03-13 Needs testing. More refactoring for save/load CAN configuration.
2021-03-13 Fix Python Config Read
2021-03-14 Add CAN Config Save/Load
2021-03-14 Remove some debug
2021-03-15 Progress. Could be brokeen.
2021-03-16 Add an optimized close loop current mode Add function callbacks for registers
2021-03-16 Starting to test multiple devices on bus
2021-03-16 coupled joint test
2021-03-17 Add some more register function callbacks. And refactor for return codes
2021-03-17 Buggy include refactor. Passing register cmd now bit cleaner.
2021-03-17 All checks. Telepresence can test. Need to put in own tests files etc
2021-03-18 PCAN Native. Very ugly test code for now
2021-03-19 Add PCAN class. Working on filtering
2021-03-19 Something has gone a bit off with the telepresense. Getting an inverted unstable control signal.
2021-03-20 Add SocketCAN. Starting NomadLBDC Lib
2021-03-21 CAN Device updates. Start Nomad Library
2021-03-21 Ready to test telepresence with new library
2021-03-21 Bug fixes. Misc Updates. Getting more usable/stable
2021-03-24 Time for a small refactor to servo wrapper class. Fix Save return code bug.
2021-03-24 Better Async support for servo
2021-03-24 More refactoring. TIme to add write/execute
2021-03-25 Add Torque mode more tweaks.
2021-03-25 Add Bus Status. Preventt control mode if position limit is activated. Add bit timing config
2021-03-25 Add additional motor to telepresense test
2021-03-27 Add JSON lib
2021-04-01 Working on control loop and tweaking registers
2021-04-01 Position and Velocity loops working decent
2021-04-01 Update TODOs
2021-04-03 Add 2 dof leg model
2021-04-04 Update Test Leg URDF
2021-04-12 Jump Test Working! Need to fix reply bug on write
2021-04-21 Update URDF
2021-04-23 Register Commadn Tweaks. Will PR this to master finally
2021-04-23 Add V2 NOMAD URDF Files w/ DAE
2021-04-27 Adjust Collision Model on URDF
2021-04-27 Full Test of new URDF + Stand.
2021-04-29 Add yaml-cpp
2021-04-29 Remove yaml-cpp link
2021-04-29 Add yaml-cpp back
2021-05-03 Add JSON
2021-05-03 Update Port Template/Function
2021-05-11 WIP. This really should be branched but pushing on
2022-01-27 Update Makefile
2022-01-28 CAN Retest
2022-02-08 Create Ubuntu install documentation
2022-02-10 Add CPU Performance setup
2022-03-03 Move Files
2022-03-03 Remove stale dir
2022-03-07 Start Python Wrapper for CAN
2022-03-07 Update gitignore and remove build files
2022-03-07 Add gitignore
2022-03-07 Update settings
2022-03-07 Update Py Wrappers
2022-03-07 Update module names
2022-03-11 Add React App
2022-03-11 Update Registers
2022-03-11 Update Ignore
2022-03-14 Front end work
2022-03-18 Start API Backend
2022-03-19 Add tinyDB
2022-03-20 Add background socket worker
2022-03-21 Front open api link + backend tweaking
2022-03-21 Update gitignore. Add python virtual environment
2022-03-21 Remove dep
2022-03-22 Connection table
